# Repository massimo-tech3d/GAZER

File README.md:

# GAZER

it's a no-hassles, sensors based, GOTO system to drive amateurial telescopes on altazimutal mounts.

No-hassles means that you setup the scope, launch the automatic calibration procedure, acquire the GPS position on your smartphone, and you are ready to aim at your desired sky objects. **No star alignement required**. **No internet connection is required**, thus it can be used in remote, dark sky location, where data services may be unavailbale.

The telescope aim is determined via magnetometer and accelerometer sensors, while corrections/precise centering are commanded manually via a Joystick.

Note that the precision of sensors, especially magnetometers, is limited to half a degree. While this is not sufficient for precision tracking, it is well enough to hit the targeted object in the field of view of a low power eyepiece.

Object Tracking is then based on precise calculations, not on the sensors readings.

The system is composed of the following components:
* Sensors for azimuth and altitude determination. These are rigidly fixed to the telscope tube or mount.
* Arduino microcontroller (Teensy 4.0 is required) which performs
	* Magnetometer calibration
	* Sensors readings
	* Calculation of Altitude and Azimuth
	* Joystick movement readouts
* a PCB to be populated with Teensy and Stepper Drivers and to plug-in sensors and joystick cables. The PCB is finally plugged in the RPi GPIO connector.
* Raspberry Pi 3 hosts the Elixir/Nerves code to
	*  control the stepper motors
	*  read the data acquired by the Teensy microcontroller
	*  execute the astronomical algorithms for aiming and tracking objects
	*  connect to the user's smartphone to acquire GPS position
	*  provides the access point to connect the smartphone to access the **Web Based GUI** for scope control.
	*  provides a full blown version of the NGC/IC catalogues and solar system object positions
* User's Smartphone
	* The user needs to install the "GPSd Forwarder" app -- opensource and available on Google Play Store -- therefore only Android phones are currently supported, however a flutter app is in the plans which will support both Android and IOS devices. No schedule available at the moment.
	* Any mobile web browser to display the GUI

More information on each component is provided in the respective folders.

## What's still to be completed - work in progress

- [ ] Unit tests
- [ ] Documentation
- [ ] Flutter application as alternative to browser based GUI

## How to build
1. download gerber files from the hardware sections and get the pcb etched by your favorite service
2. follow the instructions in hardware folder
3. flash the teensy with the sketch in arduino folder
4. plug the teensy on the PCB socket
5. plug the PCB onto the RPi3 GPIO
6. flash the RPi3 card with the nerves image provided in raspberry folder. Or, if preferred, compile the source code and use the elixir/nerves commands to flash the card
7. connect sensors and motors to the RPi box
8. boot the RPi3
9. Verify the smartphone connectivity. Select gazer access point and connect to 192.168.3.1
10. install "GPSd Forwarder" from Play Store and turn it on
11. Enjoy mant star gazing nights !

## License
the project is released under AGPLv3 License (the dependencies have their own licences)

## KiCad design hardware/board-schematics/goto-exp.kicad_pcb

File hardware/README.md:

## Hardware description
The Hardware for GAZER system is composed of following items:
* 1 x Raspberry Pi 3
* 1 x Teensy 4.0
* 1 x PCB - Gerber files available in this repository
* 2 x Stepper motor controller. Tested with DRV8825. Any other model with same pinout, and capable of 32 µsteps per step, should be ok
* 1 x Analogue Joystick with 5 pins connector, 2 axis 1 button
* 2 x 4 pins cables and connectors for the sensors
* 1 x 5 pins cable and connectors for the joystick
* 1 x MEMS Magnetometer. Suppeorted: LIS3MDL and PNI RM3100
* 1 x MEMS Accelerometer as untilter. Supported: MMA8451 and MPU6050
* 1 x MEMS Accelerometer for Attitude. Supported LSM6DSV

### PCB Assembly

The PCB shows clear indications about what needs to be plugged where. Just solder the two 100uF capacitors (beware of polarity), the sockets and pin connectors where they need to be and plug in the components.

**Note**
The 40 pin socket to the Raspberry PI needs to be positioned on the back of the PCB (solder on the front).

The two sensors sockets are interchangeable, sensors block and accelerometer can be plugged in either one.

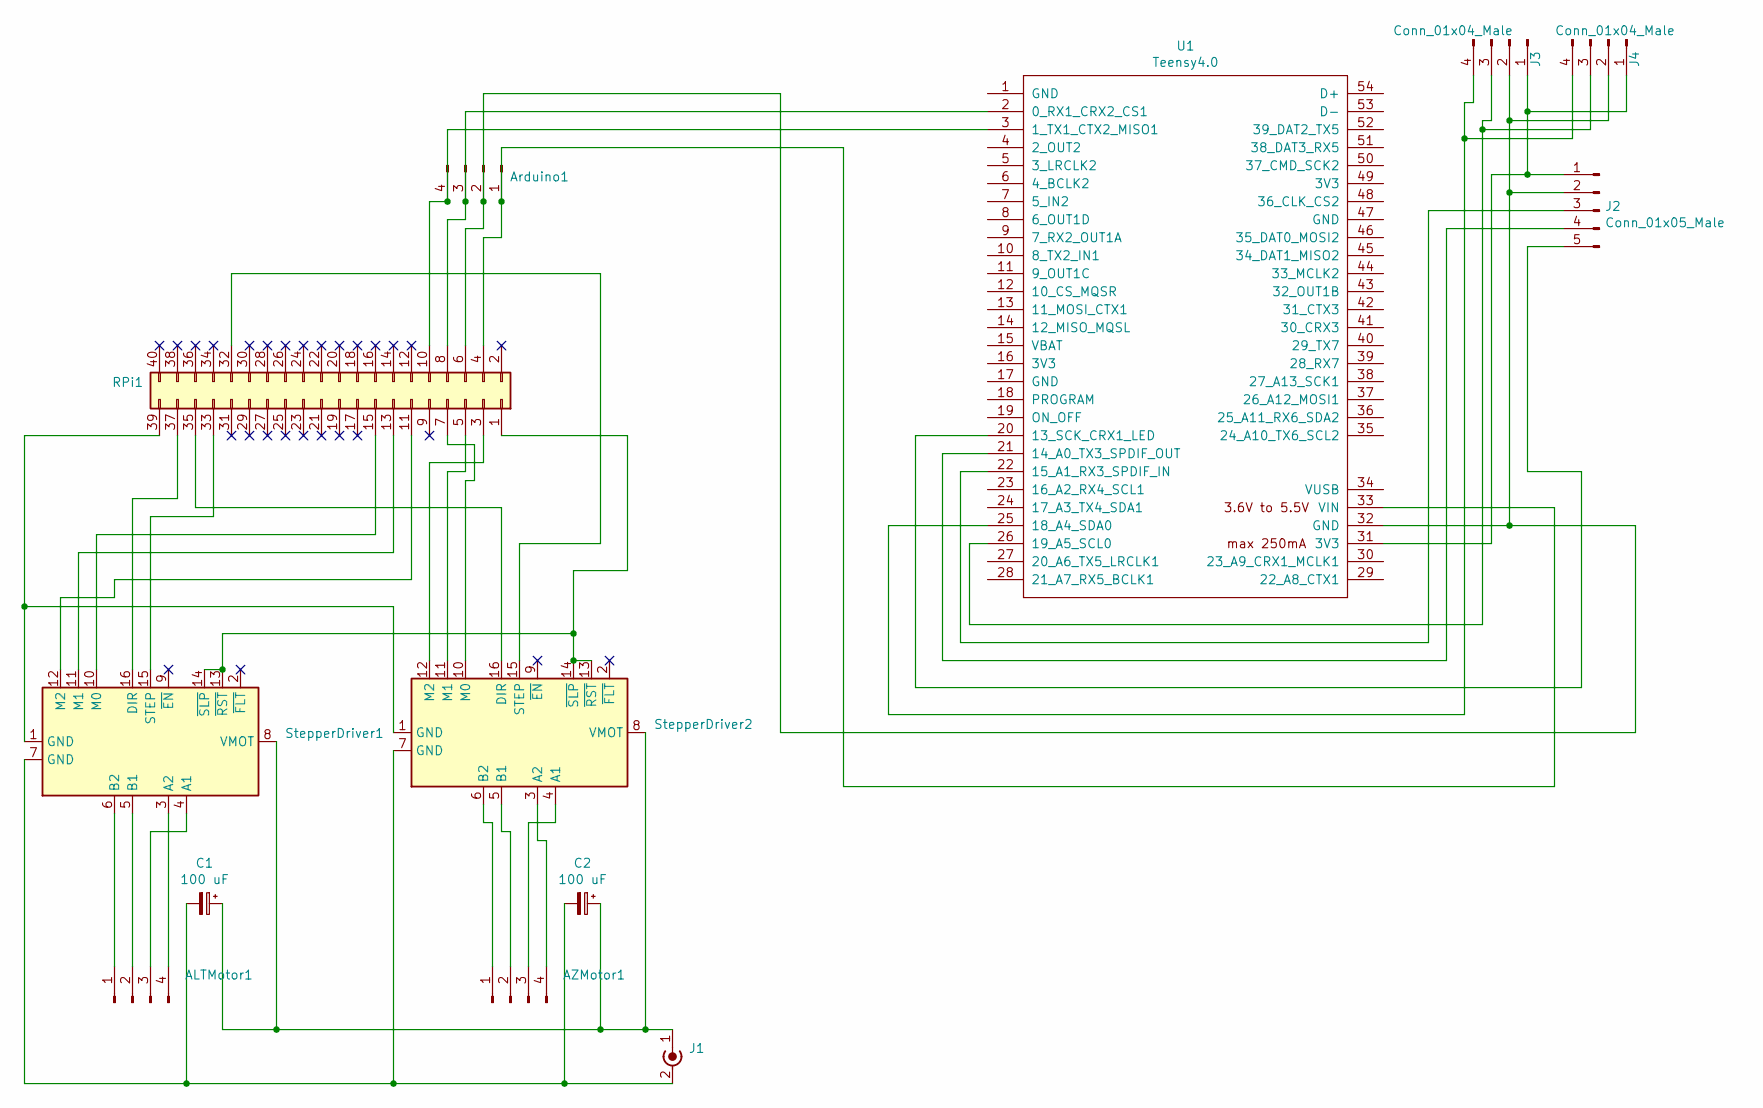
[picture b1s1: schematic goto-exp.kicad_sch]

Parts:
ALTMotor1: Conn_01x04_Male; PinHeader_1x04_P2.54mm_Vertical
AZMotor1: Conn_01x04_Male; PinHeader_1x04_P2.54mm_Vertical
Arduino1: Conn_01x04_Male; PinHeader_1x04_P2.54mm_Vertical
C1, C2: 100 uF; CP_Radial_D10.0mm_P5.00mm
J1: Conn_Coaxial_Power; PinHeader_1x02_P2.54mm_Vertical
J2: Conn_01x05_Male; PinHeader_1x05_P2.54mm_Vertical
J3, J4: Conn_01x04_Male; PinHeader_1x04_P2.54mm_Vertical
RPi1: Conn_02x20; PinSocket_2x20_P2.54mm_Vertical
StepperDriver1, StepperDriver2: Pololu_Breakout_DRV8825; Pololu_Breakout-16_15.2x20.3mm
U1: Teensy4.0; Teensy40

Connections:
unnamed: ALTMotor1.1, StepperDriver1.6 (B2)
unnamed: ALTMotor1.2, StepperDriver1.5 (B1)
unnamed: ALTMotor1.3, StepperDriver1.4 (A1)
unnamed: ALTMotor1.4, StepperDriver1.3 (A2)
unnamed: AZMotor1.1, StepperDriver2.6 (B2)
unnamed: AZMotor1.2, StepperDriver2.5 (B1)
unnamed: AZMotor1.3, StepperDriver2.4 (A1)
unnamed: AZMotor1.4, StepperDriver2.3 (A2)
unnamed 8: Arduino1.1, RPi1.4, U1.33 (VIN); also elsewhere on the board
unnamed 9: Arduino1.2, J2.2, J3.2, J4.2, RPi1.6, U1.32 (GND); also elsewhere on the board
unnamed 10: Arduino1.3, RPi1.8, U1.2 (0_RX1_CRX2_CS1); also elsewhere on the board
unnamed 11: Arduino1.4, RPi1.10, U1.3 (1_TX1_CTX2_MISO1); also elsewhere on the board
unnamed: C1.1, C2.1, J1.1 (In), StepperDriver1.8 (VMOT), StepperDriver2.8 (VMOT)
unnamed: C1.2, C2.2, J1.2 (Ext), StepperDriver1.7 (GND), StepperDriver2.7 (GND)
unnamed: J2.1, J3.1, J4.1, U1.31 (3V3)
unnamed: J2.3, U1.22 (15_A1_RX3_SPDIF_IN)
unnamed: J2.4, U1.21 (14_A0_TX3_SPDIF_OUT)
unnamed: J2.5, U1.20 (13_SCK_CRX1_LED)
unnamed: J3.3, J4.3, U1.26 (19_A5_SCL0)
unnamed: J3.4, J4.4, U1.25 (18_A4_SDA0)
unnamed 20: RPi1.1, StepperDriver1.13 (~RST), StepperDriver1.14 (~SLP), StepperDriver2.13 (~RST), StepperDriver2.14 (~SLP); also elsewhere on the board
unnamed 22: RPi1.3, StepperDriver2.12 (M2); also elsewhere on the board
unnamed 23: RPi1.5, StepperDriver2.11 (M1); also elsewhere on the board
unnamed 24: RPi1.7, StepperDriver2.10 (M0); also elsewhere on the board
unnamed 26: RPi1.11, StepperDriver1.12 (M2); also elsewhere on the board
unnamed 28: RPi1.13, StepperDriver1.11 (M1); also elsewhere on the board
unnamed 30: RPi1.15, StepperDriver1.10 (M0); also elsewhere on the board
unnamed 47: RPi1.32, StepperDriver2.15 (STEP); also elsewhere on the board
unnamed 48: RPi1.33, StepperDriver1.15 (STEP); also elsewhere on the board
unnamed 50: RPi1.35, StepperDriver2.16 (DIR); also elsewhere on the board
unnamed 52: RPi1.37, StepperDriver1.16 (DIR); also elsewhere on the board
unnamed 54: RPi1.39, StepperDriver1.1 (GND), StepperDriver2.1 (GND); also elsewhere on the board

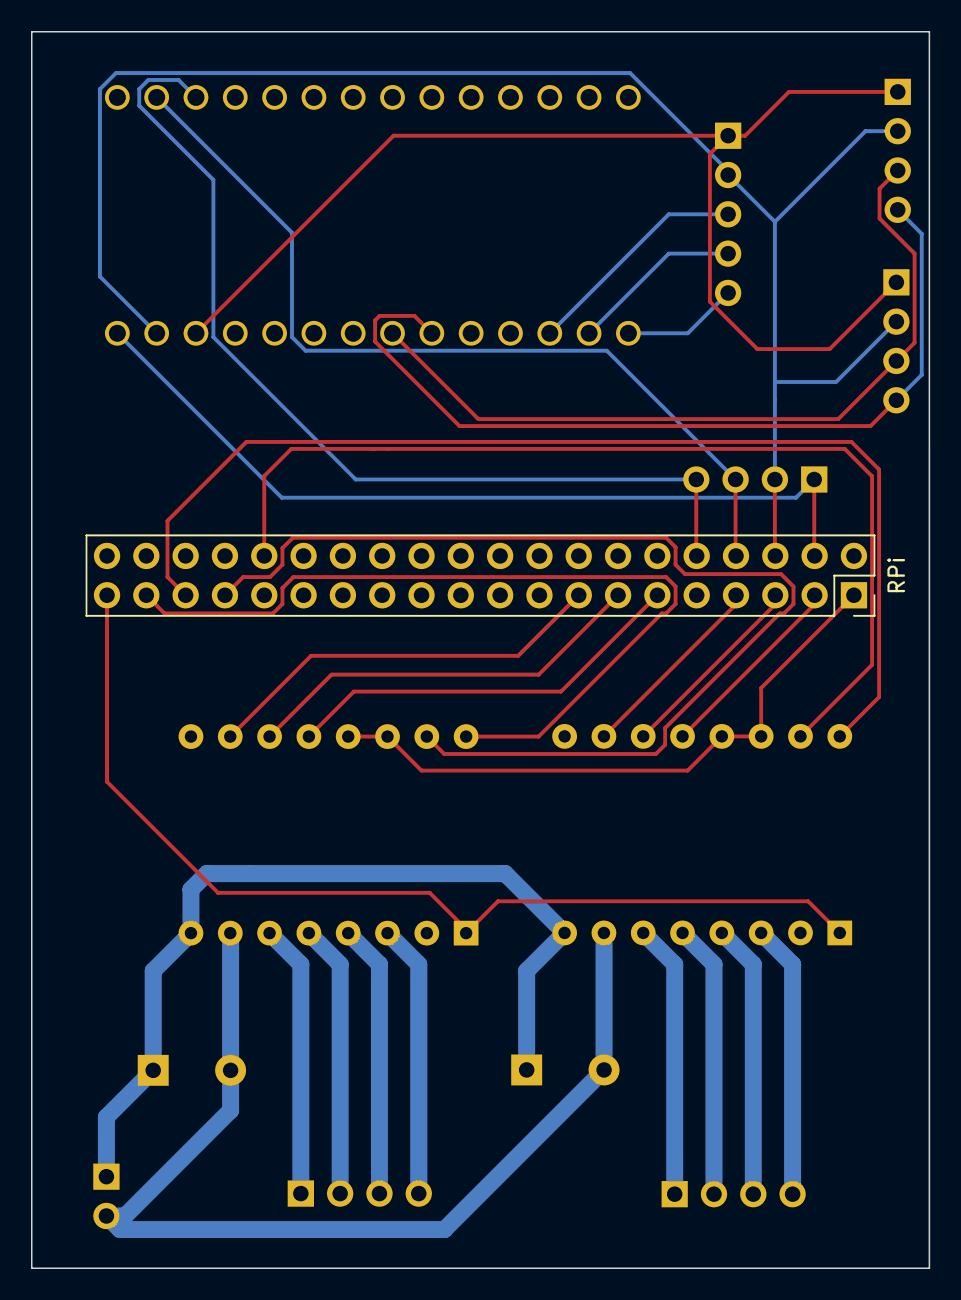
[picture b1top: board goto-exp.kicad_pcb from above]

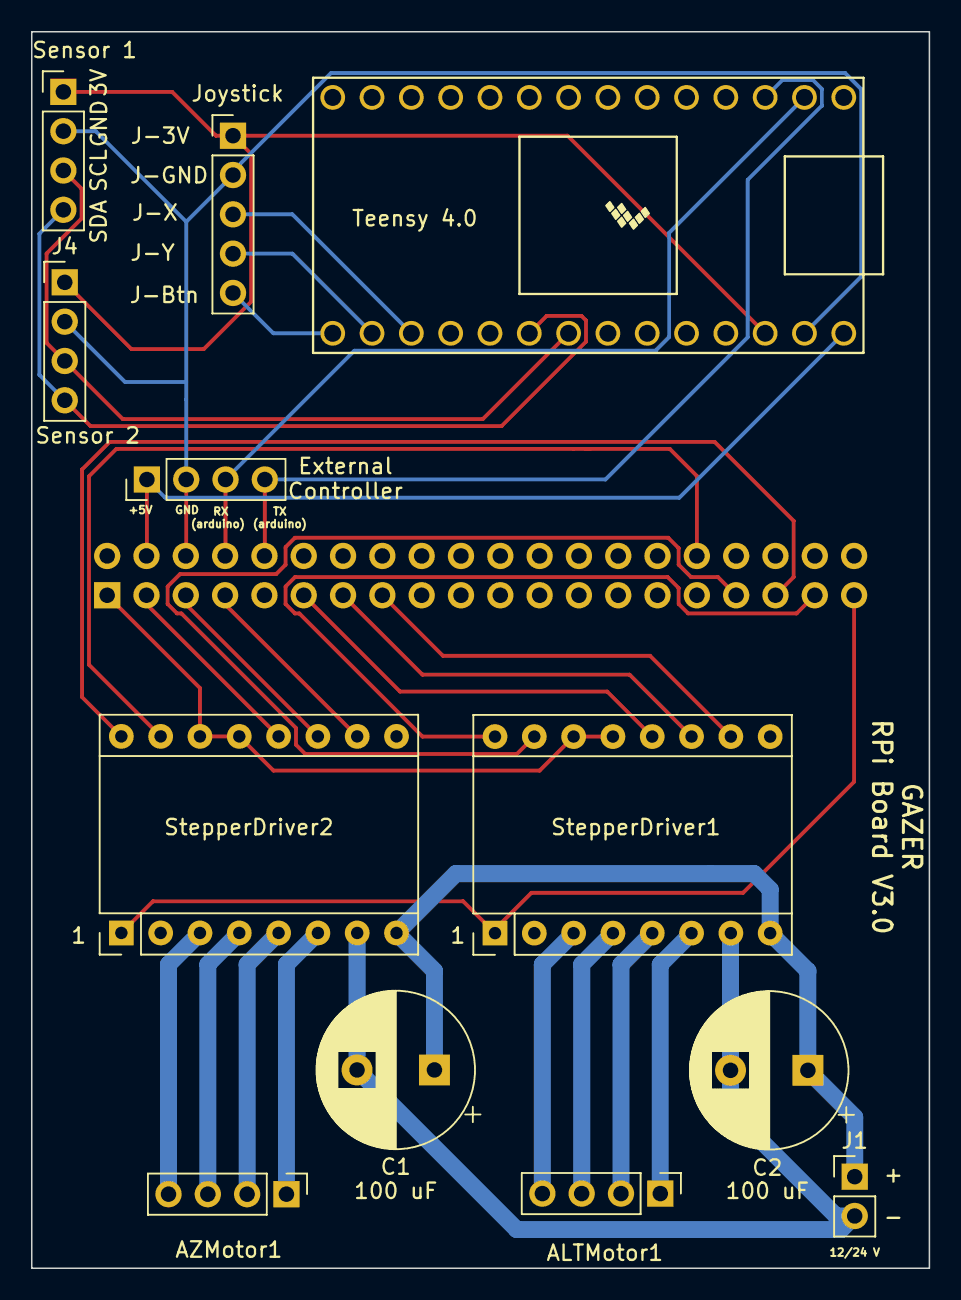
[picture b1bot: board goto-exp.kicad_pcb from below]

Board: 2 copper layers, 58.0 x 79.9 mm, 13 parts (12 on the bottom side), 32 nets.

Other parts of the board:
RPi: Conn_02x20; PinSocket_2x20_P2.54mm_Vertical

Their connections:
unnamed 8: RPi.4; also elsewhere on the board
unnamed 9: RPi.6; also elsewhere on the board
unnamed 10: RPi.8; also elsewhere on the board
unnamed 11: RPi.10; also elsewhere on the board
unnamed 20: RPi.1; also elsewhere on the board
unnamed 22: RPi.3; also elsewhere on the board
unnamed 23: RPi.5; also elsewhere on the board
unnamed 24: RPi.7; also elsewhere on the board
unnamed 26: RPi.11; also elsewhere on the board
unnamed 28: RPi.13; also elsewhere on the board
unnamed 30: RPi.15; also elsewhere on the board
unnamed 47: RPi.32; also elsewhere on the board
unnamed 48: RPi.33; also elsewhere on the board
unnamed 50: RPi.35; also elsewhere on the board
unnamed 52: RPi.37; also elsewhere on the board
unnamed 54: RPi.39; also elsewhere on the board

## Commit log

2023-01-12 arduino commit
2023-01-12 arduino readme
2023-01-12 readme
2023-01-12 Remove gitignore
2023-01-13 hardware schematics
2023-02-20 schematics
2023-02-20 license
2023-04-28 axis rotation management - first step
2023-06-16 soft/hard irons calculations improved
2023-06-20 debouncing juystick button
2023-06-24 cleanup
2023-06-24 accel calibration
2023-06-26 clean up
2023-06-26 adjusted compass kalman filter
2023-10-14 - refactored sensors management - added magnetometer compensation
2024-04-11 new untilt functionality, general cleanup
2024-04-11 removed old files
2024-04-11 gazer firmware v 0.5
2024-06-11 split sketch in 2D and 3D calibration
2024-06-11 temp
2024-06-11 readme.md
